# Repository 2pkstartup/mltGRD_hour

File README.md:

# mltGRD_hour
Firmware for enlarger controler based on RP2040

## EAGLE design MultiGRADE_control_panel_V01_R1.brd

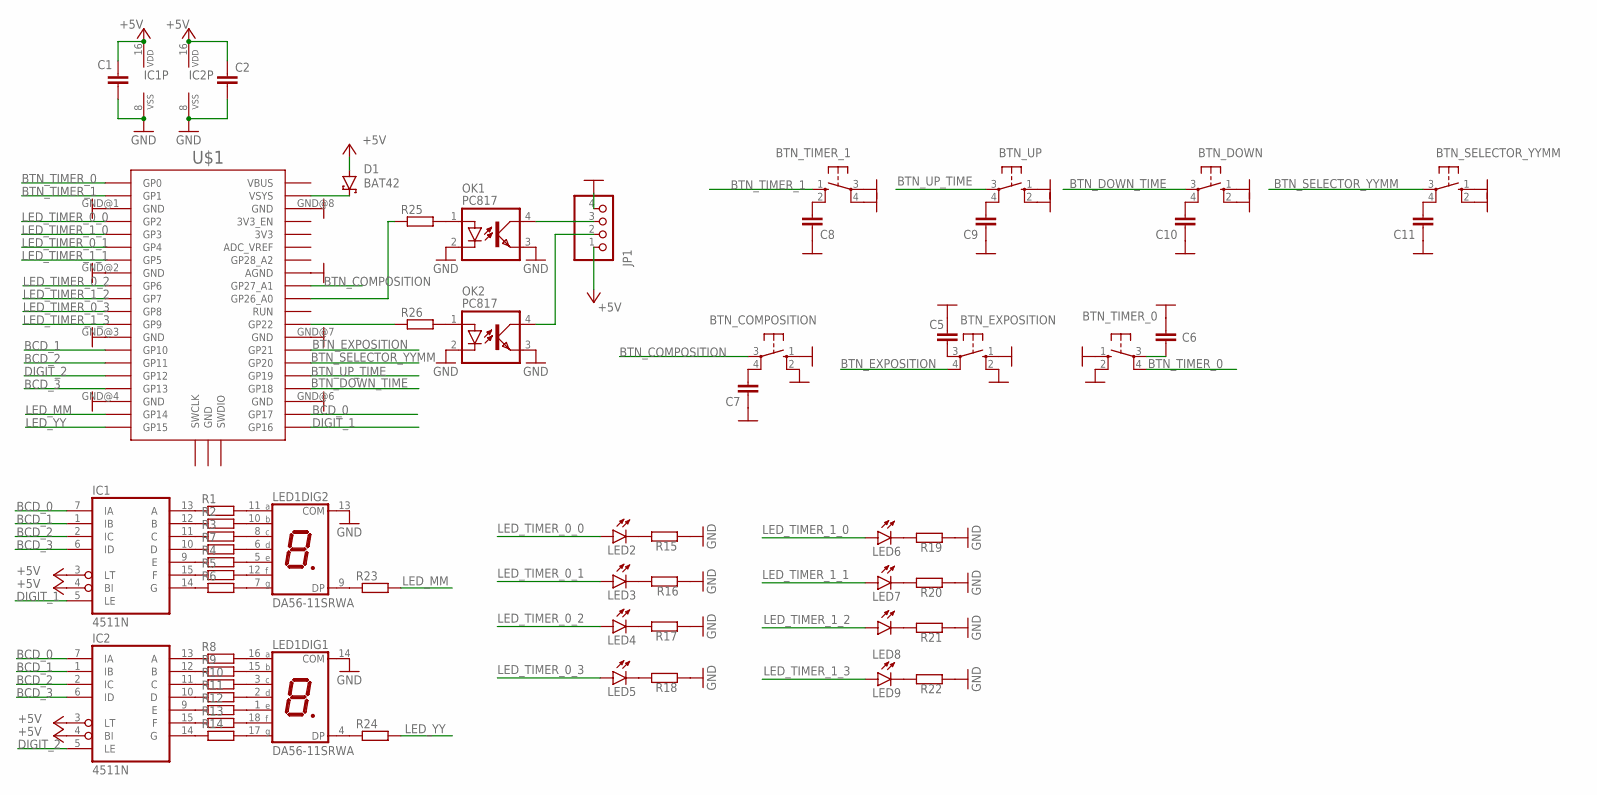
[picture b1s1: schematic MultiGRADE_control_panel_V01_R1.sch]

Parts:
BTN_COMPOSITION: 10-XX; B3F-10XX
BTN_DOWN: 10-XX; B3F-10XX
BTN_EXPOSITION: 10-XX; B3F-10XX
BTN_SELECTOR_YYMM: 10-XX; B3F-10XX
BTN_TIMER_0, BTN_TIMER_1: 10-XX; B3F-10XX
BTN_UP: 10-XX; B3F-10XX
C1, C2: C-EU050-025X075; C050-025X075
C5, C6, C7, C8, C9, C10, C11: C-EU025-025X050; C025-025X050
D1: BAT42; DO35-10
IC1, IC2: 4511N; DIL16
JP1: PINHD-1X4; 1X04
LED1: DA56-11SRWA; DA56
LED2, LED3, LED4, LED5, LED6, LED7, LED8, LED9: LED3MM
OK1, OK2: PC817; DIL04
R1, R2, R3, R4, R5, R6, R7, R8, R9, R10, R11, R12, R13, R14, R15, R16, R17, R18, R19, R20, R21, R22, R23, R24, R25, R26: R-EU_0204/7; 0204/7
U$1: RPI_PICO_IG-TH; RPI_PICO_TH

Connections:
+5V: C1.1, C2.1, D1.A, IC1.3 (LT), IC1.4 (BI), IC1.16 (VDD), IC2.3 (LT), IC2.4 (BI), IC2.16 (VDD), JP1.1
BCD_0: IC1.7 (IA), IC2.7 (IA), U$1.GP17
BCD_1: IC1.1 (IB), IC2.1 (IB), U$1.GP10
BCD_2: IC1.2 (IC), IC2.2 (IC), U$1.GP11
BCD_3: IC1.6 (ID), IC2.6 (ID), U$1.GP13
BTN_COMPOSITION: BTN_COMPOSITION.3, U$1.GP27_A1
BTN_DOWN_TIME: BTN_DOWN.3, U$1.GP18
BTN_EXPOSITION: BTN_EXPOSITION.4 (P1), U$1.GP21
BTN_SELECTOR_YYMM: BTN_SELECTOR_YYMM.3, U$1.GP20
BTN_TIMER_0: BTN_TIMER_0.4 (P1), U$1.GP0
BTN_TIMER_1: BTN_TIMER_1.1 (S), U$1.GP1
BTN_UP_TIME: BTN_UP.3, U$1.GP19
DIGIT_1: IC1.5 (LE), U$1.GP16
DIGIT_2: IC2.5 (LE), U$1.GP12
GND: BTN_COMPOSITION.1 (S), BTN_COMPOSITION.2 (S1), BTN_DOWN.1 (S), BTN_DOWN.2 (S1), BTN_EXPOSITION.1 (S), BTN_EXPOSITION.2 (S1), BTN_SELECTOR_YYMM.1 (S), BTN_SELECTOR_YYMM.2 (S1), BTN_TIMER_0.1 (S), BTN_TIMER_0.2 (S1), BTN_TIMER_1.3, BTN_TIMER_1.4 (P1), BTN_UP.1 (S), BTN_UP.2 (S1), C1.2, C2.2, C5.1, C6.1, C7.1, C8.1, C9.1, C10.1, C11.1, IC1.8 (VSS), IC2.8 (VSS), JP1.4, LED1.13 (COM), LED1.14 (COM), OK1.2 (C), OK1.3 (EMIT), OK2.2 (C), OK2.3 (EMIT), R15.1, R16.1, R17.1, R18.1, R19.1, R20.1, R21.1, R22.1, U$1.AGND, U$1.GND@1 (GND), U$1.GND@2 (GND), U$1.GND@3 (GND), U$1.GND@4 (GND), U$1.GND@6 (GND), U$1.GND@7 (GND), U$1.GND@8 (GND)
LED_MM: R23.2, U$1.GP14
LED_TIMER_0_0: LED2.A, U$1.GP2
LED_TIMER_0_1: LED3.A, U$1.GP4
LED_TIMER_0_2: LED4.A, U$1.GP6
LED_TIMER_0_3: LED5.A, U$1.GP8
LED_TIMER_1_0: LED6.A, U$1.GP3
LED_TIMER_1_1: LED7.A, U$1.GP5
LED_TIMER_1_2: LED8.A, U$1.GP7
LED_TIMER_1_3: LED9.A, U$1.GP9
LED_YY: R24.2, U$1.GP15
unnamed: IC1.13 (A), R1.1
unnamed: IC1.11 (C), R3.1
unnamed: IC1.15 (F), R5.1
unnamed: IC1.14 (G), R6.1
unnamed: IC1.10 (D), R7.1
unnamed: IC2.13 (A), R8.1
unnamed: IC2.12 (B), R9.1
unnamed: IC2.11 (C), R10.1
unnamed: IC2.10 (D), R11.1
unnamed: IC2.9 (E), R12.1
unnamed: IC2.15 (F), R13.1
unnamed: IC2.14 (G), R14.1
unnamed: LED1.16 (A), R8.2
unnamed: LED1.15 (B), R9.2
unnamed: LED1.3 (C), R10.2
unnamed: LED1.2 (D), R11.2
unnamed: LED1.1 (E), R12.2
unnamed: LED1.18 (F), R13.2
unnamed: LED1.17 (G), R14.2
unnamed: IC1.9 (E), R4.1
unnamed: IC1.12 (B), R2.1
unnamed: LED1.11 (A), R1.2
unnamed: LED1.10 (B), R2.2
unnamed: LED1.8 (C), R3.2
unnamed: LED1.5 (E), R4.2
unnamed: LED1.12 (F), R5.2
unnamed: LED1.7 (G), R6.2
unnamed: LED1.6 (D), R7.2
unnamed: LED2.K (C), R15.2
unnamed: LED1.9 (DP), R23.1
unnamed: BTN_EXPOSITION.3, C5.2
unnamed: BTN_TIMER_0.3, C6.2
unnamed: BTN_COMPOSITION.4 (P1), C7.2
unnamed: BTN_TIMER_1.2 (S1), C8.2
unnamed: BTN_UP.4 (P1), C9.2
unnamed: BTN_DOWN.4 (P1), C10.2
unnamed: BTN_SELECTOR_YYMM.4 (P1), C11.2
unnamed: LED1.4 (DP), R24.1
unnamed: R25.1, U$1.GP26_A0
unnamed: OK1.1 (A), R25.2
unnamed: OK2.1 (A), R26.2
unnamed: JP1.3, OK1.4 (COL)
unnamed: JP1.2, OK2.4 (COL)
unnamed: R26.1, U$1.GP22
unnamed: D1.C, U$1.VSYS
unnamed: LED3.K (C), R16.2
unnamed: LED4.K (C), R17.2
unnamed: LED5.K (C), R18.2
unnamed: LED6.K (C), R19.2
unnamed: LED7.K (C), R20.2
unnamed: LED8.K (C), R21.2
unnamed: LED9.K (C), R22.2

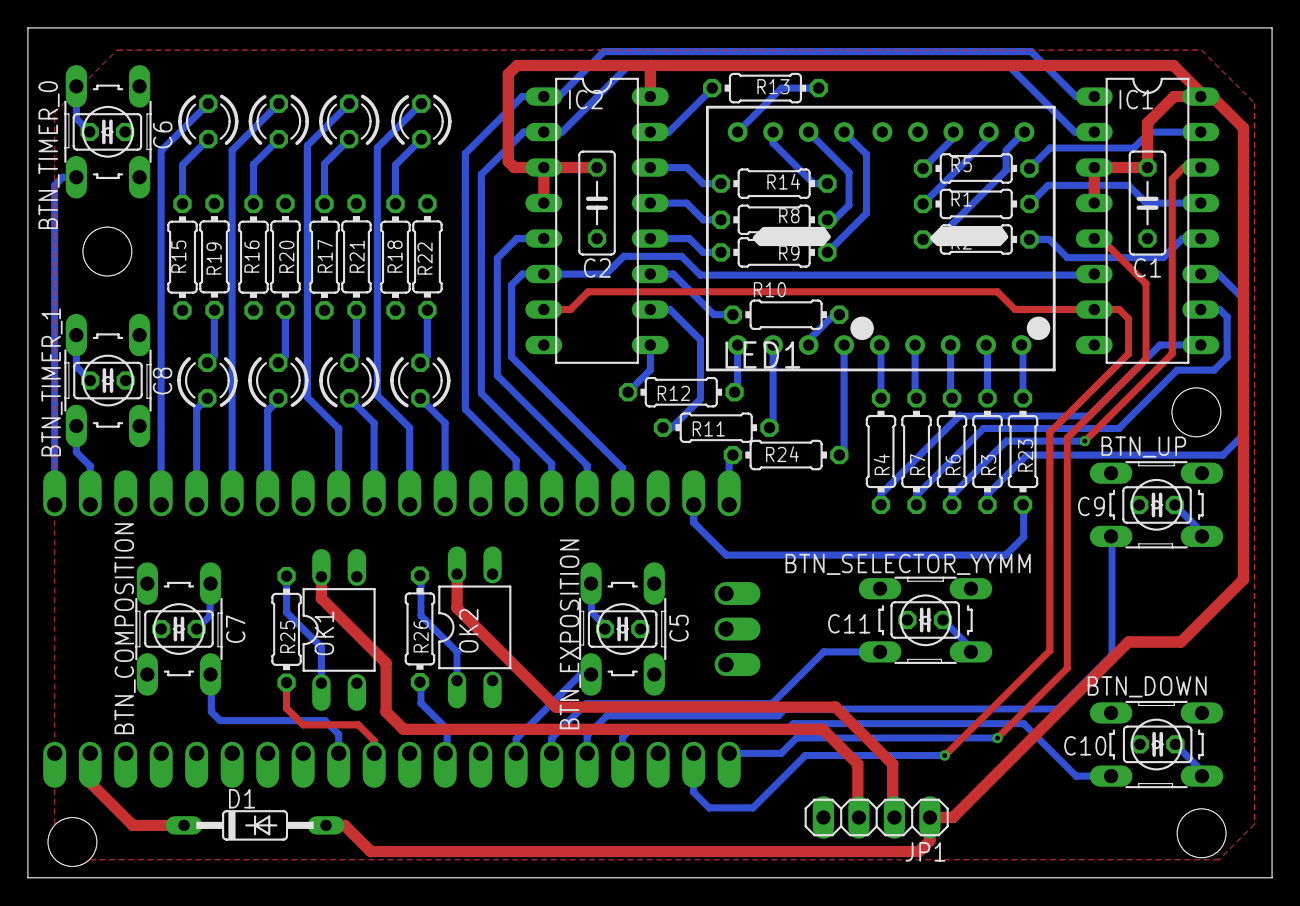
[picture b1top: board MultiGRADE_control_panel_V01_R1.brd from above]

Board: 2 copper layers, 89.0 x 60.8 mm, 58 parts (1 on the bottom side), 77 nets.

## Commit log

2024-02-28 Main control PCB - Eagle 9.0 files
